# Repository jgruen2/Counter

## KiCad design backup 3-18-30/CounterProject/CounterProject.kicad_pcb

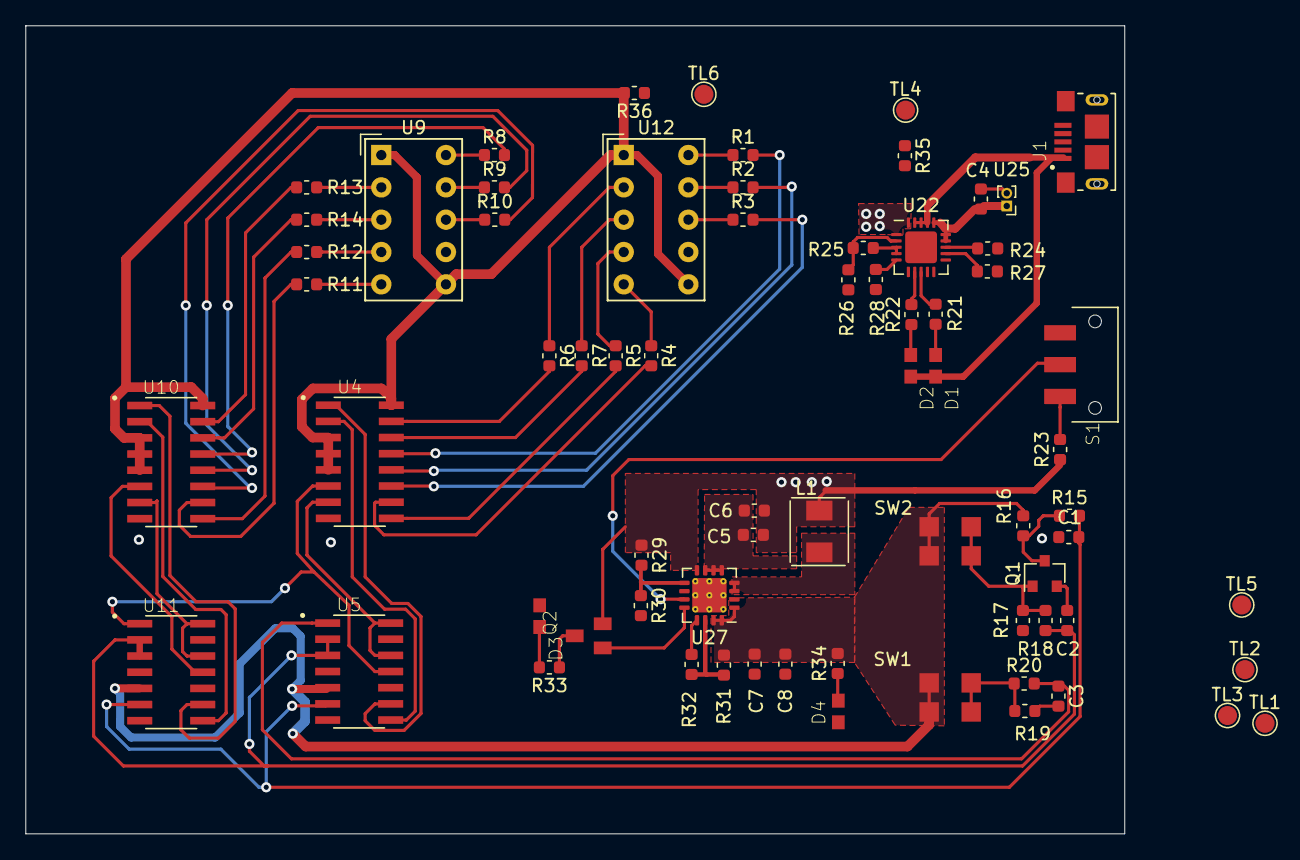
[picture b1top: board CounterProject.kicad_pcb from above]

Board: 2 copper layers, 86.4 x 63.5 mm, 70 parts (0 on the bottom side), 64 nets.

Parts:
C1, C2, C3, C6: 0.1uF; C_0603_1608Metric
C4, C5: 10uF; C_0603_1608Metric
C7: 2.2uF; C_0603_1608Metric
C8: 100uF; C_0603_1608Metric
D1, D2, D3, D4: LED; LTST-C193KGKT-5A - 0603
J1: USB_B_Micro; FCI_10118193-0001LF
L1: 6.8uH; SD43-562
Q1: BSS138; SOT-23
Q2: MMUN2133LT1G; SOT95P240X111-3N
R1, R2, R3, R4, R5, R6, R7, R8, R9, R10, R11, R12, R13, R14: 3.3k; R_0603_1608Metric
R15, R17, R18, R19, R20: 10k; R_0603_1608Metric
R16, R23, R26, R27, R35, R36: 100k; R_0603_1608Metric
R21, R22, R24, R33, R34: 1k; R_0603_1608Metric
R25: 270k; R_0603_1608Metric
R28: 16k; R_0603_1608Metric
R29: 1.87M; R_0603_1608Metric
R30: 340k; R_0603_1608Metric
R31: 1.07M; R_0603_1608Metric
R32: 200k; R_0603_1608Metric
S1: JS102011SAQN; SW_JS102011SAQN
SW1, SW2: SW_Push; Push Button - 1241.1601.11
TL1, TL2, TL3, TL4, TL5, TL6: TestLoop; TestPoint_Pad_D1.5mm
U4, U10: 74LS47; SN74LS47D - SOIC127P600X175-16N
U5, U11: 74LS90; SN74LS90DR - SOIC127P600X175-14N
U9, U12: HDSP-A151
U22: MCP73871; QFN-20-1EP_4x4mm_P0.5mm_EP2.5x2.5mm
U25: Header; PinHeader_1x02_P1.00mm_Vertical
U27: TPS61090; Texas_S-PVQFN-N16_EP2.7x2.7mm_ThermalVias

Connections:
+5V: C7.1, C8.1, R16.2, R31.1, R34.2, R36.2, SW1.2, SW2.2, U4.3, U4.4, U4.5, U4.16, U5.5, U9.1, U9.6, U10.3, U10.4, U10.5, U10.16, U11.5, U12.1, U12.6, U27.1, U27.15, U27.16
+BATT: C5.1, C6.1, L1.1, Q2.2, R23.1, R29.1, R35.2, U22.1, U22.20, U27.8
/A1: U4.7, U5.12, U5.14
/A2: U10.7, U11.12, U11.14
/B1: U4.1, U5.9
/B2: U10.1, U11.9
/C1: U4.2, U5.8
/C2: U10.2, U11.8
/D1: U4.6, U5.11, U11.1
/D2: U10.6, U11.11
/Power/EN: S1.2, U27.11
/Push: C3.1, R20.2, U5.1
/Reset: C2.1, R18.2, U5.2, U5.3, U11.2, U11.3
/Reset_GND: C1.1, R15.2, U5.6, U11.6
GND: C1.2, C2.2, C3.2, C4.2, C5.2, C6.2, C7.2, C8.2, D3.1, D4.1, J1.5, Q1.2, R17.2, R19.2, R24.2, R26.2, R27.2, R28.2, R30.2, R32.2, S1.3, U4.8, U5.10, U10.8, U11.10, U22.10, U22.11, U22.21, U25.2, U27.5, U27.6, U27.7, U27.10, U27.13, U27.17
unnamed: C4.1, U22.14, U22.15, U22.16, U25.1
unnamed: D1.1, R21.1
unnamed: D2.1, R22.1
unnamed: D3.2, R33.2
unnamed: D4.2, R34.1
unnamed: L1.2, U27.3, U27.4
unnamed: Q1.1, R17.1, R18.1, SW2.1
unnamed: Q1.3, R15.1, R16.1
unnamed: Q2.1, U27.12
unnamed: Q2.3, R33.1
unnamed: R1.1, U12.10
unnamed: R1.2, U4.13
unnamed: R2.1, U12.9
unnamed: R2.2, U4.12
unnamed: R3.1, U12.8
unnamed: R3.2, U4.11
unnamed: R4.1, U12.5
unnamed: R4.2, U4.10
unnamed: R5.1, U12.4
unnamed: R5.2, U4.9
unnamed: R6.1, U12.2
unnamed: R6.2, U4.15
unnamed: R7.1, U12.3
unnamed: R7.2, U4.14
unnamed: R8.1, U9.10
unnamed: R8.2, U10.13
unnamed: R9.1, U9.9
unnamed: R9.2, U10.12
unnamed: R10.1, U9.8
unnamed: R10.2, U10.11
unnamed: R11.1, U9.5
unnamed: R11.2, U10.10
unnamed: R12.1, U9.4
unnamed: R12.2, U10.9
unnamed: R13.1, U9.2
unnamed: R13.2, U10.15
unnamed: R14.1, U9.3
unnamed: R14.2, U10.14
unnamed: R19.1, R20.1, SW1.1
unnamed: R21.2, U22.8
unnamed: R22.2, U22.7
unnamed: R23.2, S1.1
unnamed: R24.1, U22.13
unnamed: R25.2, R26.1, U22.2
unnamed: R27.1, U22.12
unnamed: R28.1, U22.5
unnamed: R29.2, R30.1, U27.9
unnamed: R31.2, R32.1, U27.14
VBUS: D1.2, D2.2, J1.1, R25.1, U22.3, U22.4, U22.9, U22.17, U22.18, U22.19

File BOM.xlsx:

Column1 | Column2 | Column3 | Column4 | Column5
Reference | Value | Footprint | Datasheet | Cost
U4 | 74LS47 | 1_Jons_Footprints:SN74LS47D - SOIC127P600X175-16N | http://www.ti.com/lit/gpn/sn74LS47 | 1.77
R7 | 3.3k | Resistor_SMD:R_0603_1608Metric | ~ | 0.1
R6 | 3.3k | Resistor_SMD:R_0603_1608Metric | ~ | 0.1
R5 | 3.3k | Resistor_SMD:R_0603_1608Metric | ~ | 0.1
R4 | 3.3k | Resistor_SMD:R_0603_1608Metric | ~ | 0.1
R3 | 3.3k | Resistor_SMD:R_0603_1608Metric | ~ | 0.1
R2 | 3.3k | Resistor_SMD:R_0603_1608Metric | ~ | 0.1
R1 | 3.3k | Resistor_SMD:R_0603_1608Metric | ~ | 0.1
U5 | 74LS90 | 1_Jons_Footprints:SN74LS90DR - SOIC127P600X175-14N | http://www.ti.com/lit/gpn/sn74LS90 | 2.25
SW1 | SW_Push | 1_Jons_Footprints:Push Button - 1241.1601.11 | https://us.schurter.com/bundles/snceschurter/epim/_ProdPool_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 | 0.31
R19 | 10k | Resistor_SMD:R_0603_1608Metric | ~ | 0.02
U12 | HDSP-A151 | Display_7Segment:HDSP-A151 | https://docs.broadcom.com/docs/AV02-2553EN | 3.25
U10 | 74LS47 | 1_Jons_Footprints:SN74LS47D - SOIC127P600X175-16N | http://www.ti.com/lit/gpn/sn74LS47 | 1.77
R14 | 3.3k | Resistor_SMD:R_0603_1608Metric | ~ | 0.23
R13 | 3.3k | Resistor_SMD:R_0603_1608Metric | ~ | 0.23
R12 | 3.3k | Resistor_SMD:R_0603_1608Metric | ~ | 0.23
R11 | 3.3k | Resistor_SMD:R_0603_1608Metric | ~ | 0.23
R10 | 3.3k | Resistor_SMD:R_0603_1608Metric | ~ | 0.23
R9 | 3.3k | Resistor_SMD:R_0603_1608Metric | ~ | 0.23
R8 | 3.3k | Resistor_SMD:R_0603_1608Metric | ~ | 0.23
U11 | 74LS90 | 1_Jons_Footprints:SN74LS90DR - SOIC127P600X175-14N | http://www.ti.com/lit/gpn/sn74LS90 | 2.25
U9 | HDSP-A151 | Display_7Segment:HDSP-A151 | https://docs.broadcom.com/docs/AV02-2553EN | 3.25
R20 | 10k | Resistor_SMD:R_0603_1608Metric | ~ | 0.02
C3 | 0.1uF | Capacitor_SMD:C_0603_1608Metric | ~ | 0.03
R18 | 10k | Resistor_SMD:R_0603_1608Metric | ~ | 0.02
C2 | 0.1uF | Capacitor_SMD:C_0603_1608Metric | ~ | 0.03
R17 | 10k | Resistor_SMD:R_0603_1608Metric | ~ | 0.02
SW2 | SW_Push | 1_Jons_Footprints:Push Button - 1241.1601.11 | https://us.schurter.com/bundles/snceschurter/epim/_ProdPool_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 | 0.31
R16 | 100k | Resistor_SMD:R_0603_1608Metric | ~ | 0.15
Q1 | BSS138 | Package_TO_SOT_SMD:SOT-23 | https://www.fairchildsemi.com/datasheets/BS/BSS138.pdf | 0.26
R15 | 10k | Resistor_SMD:R_0603_1608Metric | ~ | 0.02
C1 | 0.1uF | Capacitor_SMD:C_0603_1608Metric | ~ | 0.03
TP1 | TestPoint | TestPoint:TestPoint_Pad_D1.0mm | ~ | 0
TP2 | TestPoint | TestPoint:TestPoint_Pad_D1.0mm | ~ | 0
TP3 | TestPoint | TestPoint:TestPoint_Pad_D1.0mm | ~ | 0
H2 | MountingHole_Pad | MountingHole:MountingHole_2.5mm_Pad | ~ | 0
H1 | MountingHole_Pad | MountingHole:MountingHole_2.5mm_Pad | ~ | 0
H3 | MountingHole_Pad | MountingHole:MountingHole_2.5mm_Pad | ~ | 0
H4 | MountingHole_Pad | MountingHole:MountingHole_2.5mm_Pad | ~ | 0
C9 | 0.1uF | Capacitor_SMD:C_0603_1608Metric | ~ | 0.03
C14 | 0.1uF | Capacitor_SMD:C_0603_1608Metric | ~ | 0.03
C10 | 0.1uF | Capacitor_SMD:C_0603_1608Metric | ~ | 0.03
C11 | 0.1uF | Capacitor_SMD:C_0603_1608Metric | ~ | 0.03
C12 | 0.1uF | Capacitor_SMD:C_0603_1608Metric | ~ | 0.03
C13 | 0.1uF | Capacitor_SMD:C_0603_1608Metric | ~ | 0.03
C20 | 0.1uF | Capacitor_SMD:C_0603_1608Metric | ~ | 0.03
TP6 | TestPoint | TestPoint:TestPoint_Pad_D1.0mm | ~ | 0
TP5 | TestPoint | TestPoint:TestPoint_Pad_D1.0mm | ~ | 0
TP4 | TestPoint | TestPoint:TestPoint_Pad_D1.0mm | ~ | 0
R35 | 100k | Resistor_SMD:R_0603_1608Metric | ~ | 0.15
R36 | 100k | Resistor_SMD:R_0603_1608Metric | ~ | 0.15
S1 | JS102011SAQN | 1_Jons_Footprints:SW_JS102011SAQN | https://dznh3ojzb2azq.cloudfront.net/products/Slide/JS/docum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 | 1.41
Q2 | MMUN2133LT1G | 1_Jons_Footprints:SOT95P240X111-3N | https://www.onsemi.com/pub/Collateral/DTA143Z-D.PDF | 0.12
L1 | 6.8uH | 1_Jons_Footprints:SD43-562 | https://www.mouser.com/datasheet/2/597/sd43-774587.pdf
R34 | 1k | Resistor_SMD:R_0603_1608Metric | ~ | 0.02
C6 | 0.1uF | Capacitor_SMD:C_0603_1608Metric | ~ | 0.03
C5 | 10uF | Capacitor_SMD:C_0603_1608Metric | ~ | 0.13
C8 | 100uF | Capacitor_SMD:C_0603_1608Metric | ~ | 0.76
C7 | 2.2uF | Capacitor_SMD:C_0603_1608Metric | ~ | 0.14000000000000001
U22 | MCP73871 | Package_DFN_QFN:QFN-20-1EP_4x4mm_P0.5mm_EP2.5x2.5mm | http://www.mouser.com/ds/2/268/22090a-52174.pdf | 1.79
R21 | 1k | Resistor_SMD:R_0603_1608Metric | ~ | 0.02
D2 | LED | 1_Jons_Footprints:LTST-C193KGKT-5A - 0603 | https://vcclite.com/wp-content/uploads/wpallimport/files/fil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 | 0.28999999999999998
D1 | LED | 1_Jons_Footprints:LTST-C193KGKT-5A - 0603 | https://vcclite.com/wp-content/uploads/wpallimport/files/fil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 | 0.28999999999999998
U25 | Header | 1_Jons_Footprints:Battery Header |  | 0
C4 | 10uF | Capacitor_SMD:C_0603_1608Metric | ~ | 0.13
R22 | 1k | Resistor_SMD:R_0603_1608Metric | ~ | 0.02
R24 | 1k | Resistor_SMD:R_0603_1608Metric | ~ | 0.02
R27 | 100k | Resistor_SMD:R_0603_1608Metric | ~ | 0.15
R25 | 270k | Resistor_SMD:R_0603_1608Metric | ~ | 0.17
R28 | 16k | Resistor_SMD:R_0603_1608Metric | ~ | 0.34
D4 | LED | 1_Jons_Footprints:LTST-C193KGKT-5A - 0603 | https://vcclite.com/wp-content/uploads/wpallimport/files/fil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 | 0.28999999999999998
R30 | 340k | Resistor_SMD:R_0603_1608Metric | ~ | 0.11
R29 | 1.87M | Resistor_SMD:R_0603_1608Metric | ~ | 0.11
R23 | 100k | Resistor_SMD:R_0603_1608Metric | ~ | 0.15
R33 | 1k | Resistor_SMD:R_0603_1608Metric | ~ | 0.02
R31 | 1.07M | Resistor_SMD:R_0603_1608Metric | ~ | 0.11
R32 | 200k | Resistor_SMD:R_0603_1608Metric | ~ | 0.34
D3 | LED | 1_Jons_Footprints:LTST-C193KGKT-5A - 0603 | https://vcclite.com/wp-content/uploads/wpallimport/files/fil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 | 0.28999999999999998
R26 | 100k | Resistor_SMD:R_0603_1608Metric | ~ | 0.15
U27 | TPS61090 | Package_DFN_QFN:Texas_S-PVQFN-N16_EP2.7x2.7mm_ThermalVias | http://www.ti.com/lit/ds/symlink/tps61090.pdf | 2.34
J1 | MicroUSB | 1_Jons_Footprints:FCI_10118193-0001LF | https://cdn.amphenol-icc.com/media/wysiwyg/files/documentati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 | 0.43

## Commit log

2020-07-11 Rev02 Update
    This update has the rev 02 schematic and layout. The board was ordered from OshPark
